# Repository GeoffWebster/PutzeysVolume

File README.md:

Bruno Putzeys Balanced Volume Control / MAS6116 Digital Control
===============================================================

KiCad V8 files for Bruno Putzeys Balanced Pre-amp with integrated MAS6116 Digital Volume Control Chip.

Circuit modifications from original design includes
* Addition of MAS6116 digital Stereo Volume Control in place of dual linear 10Kohm potentiometer
* Addition of inverting unity gain amplifier driver for driven signal for - output pin. Original was balanced output impedance only
* Addition of Unbalanced output (X5) to provide input to headphone amplifier

Original Bruno Putzeys preamplifier used qty 4 of LM4562 + qty 1 of TL072 (as servo)
Alternatives to LM4562 include
* OPA1642AIDR  595-OPA1642AIDR
* OPA1656ID    595-OPA1656ID

Addition of inverting amplifiers within balanced output (Vout-) adds following components into overall circuit:
U7, U8 OPA1656
R38-41 12K 0805 Thin Film
C28, C29 47pF **DNF**

Addition of unbalanced output for use by external headphone amplifier added connector X5 only.

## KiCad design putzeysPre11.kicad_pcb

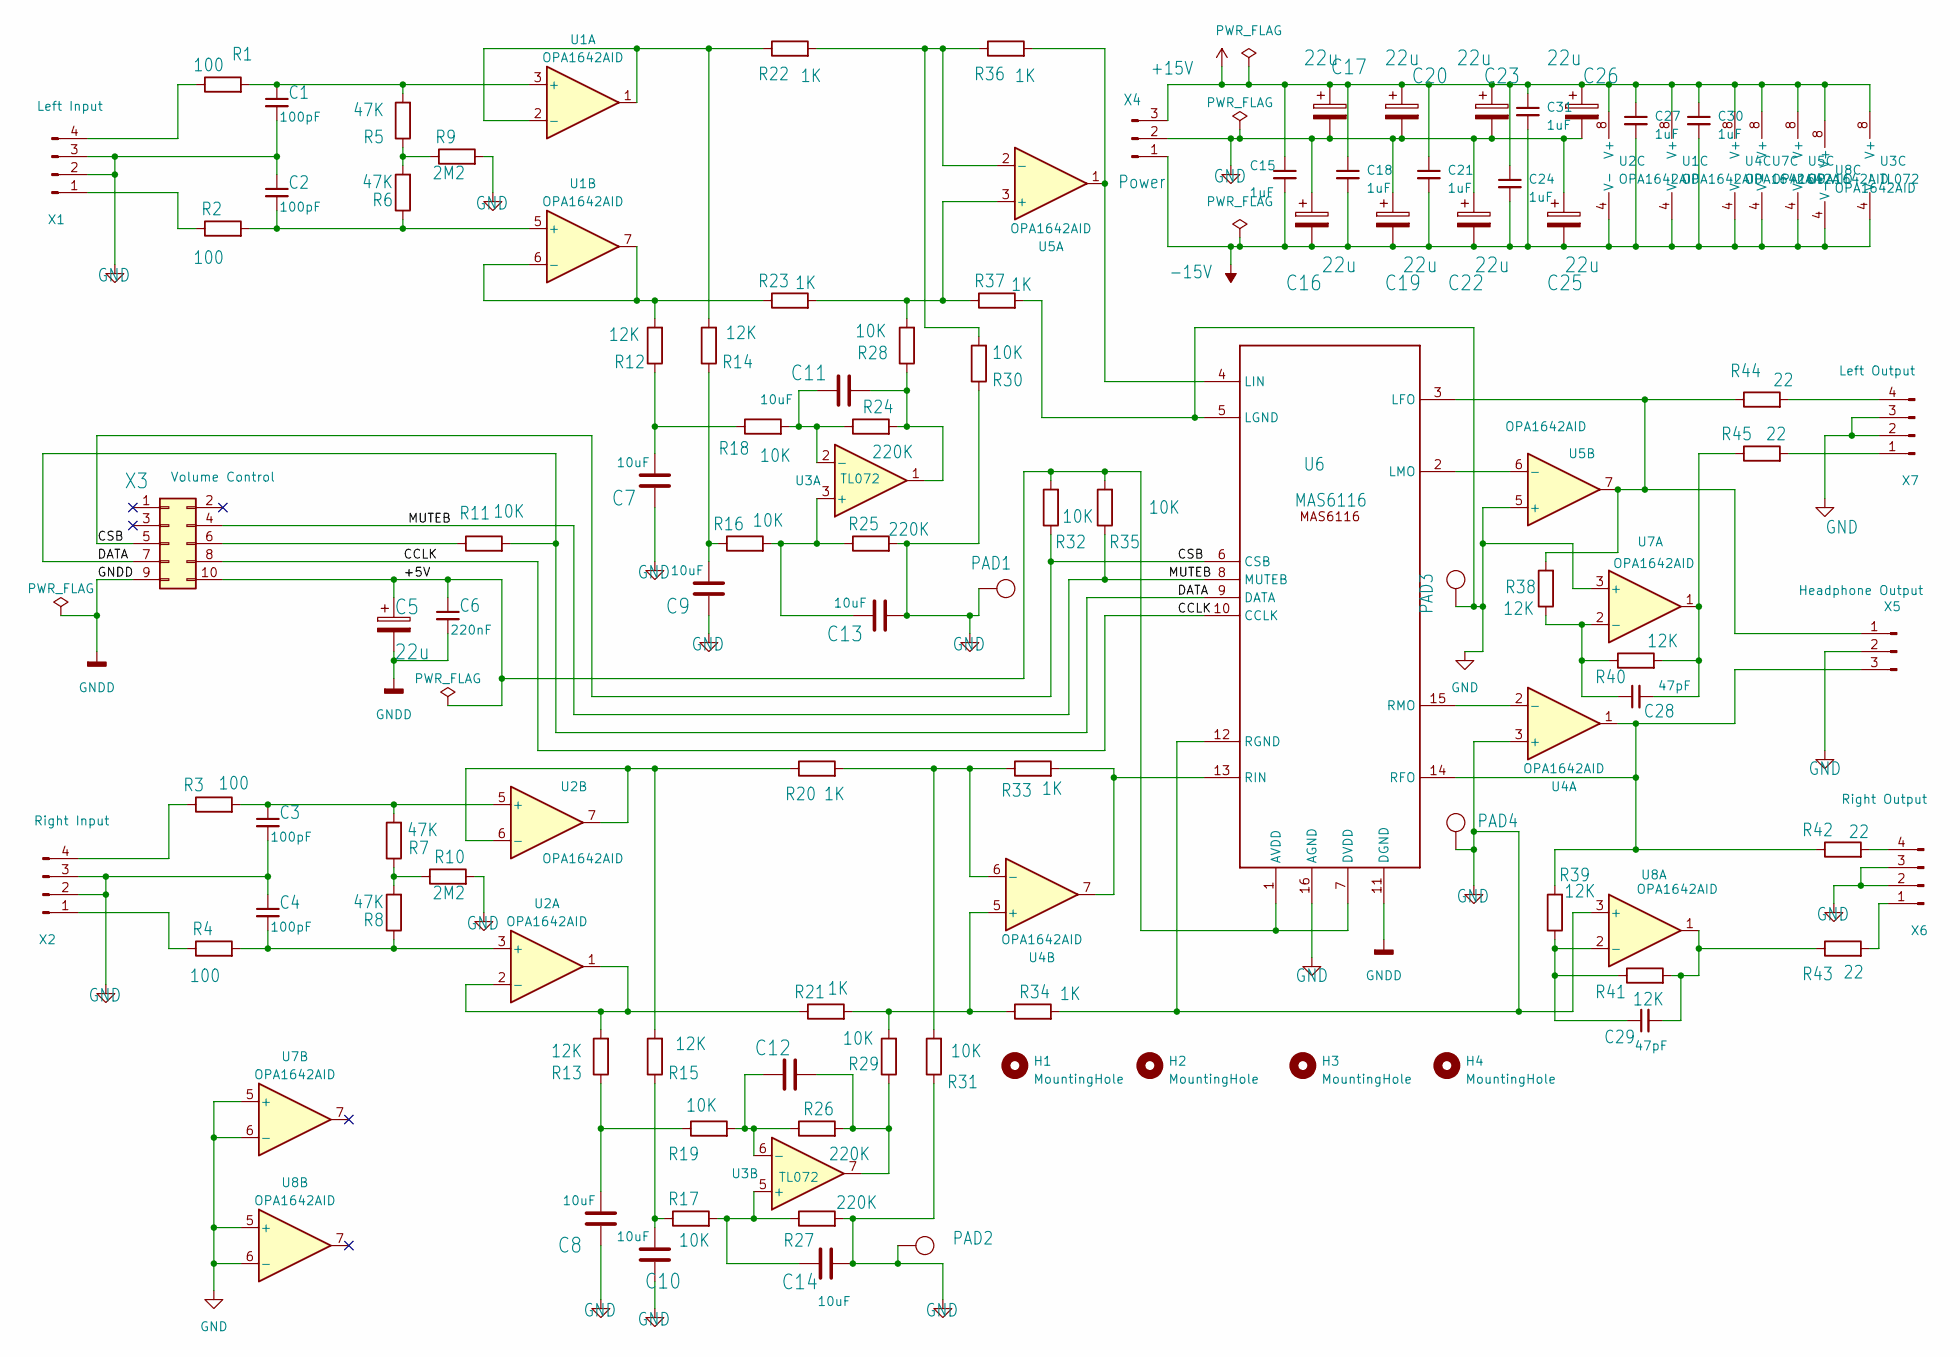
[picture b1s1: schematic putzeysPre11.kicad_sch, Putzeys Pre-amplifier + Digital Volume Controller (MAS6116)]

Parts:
C1, C2, C3, C4: 100pF; C_0805_2012Metric
C5, C16, C17, C19, C20, C22, C23, C25, C26: 22u; CP_Radial_D5.0mm_P2.00mm
C6: 220nF; C_0805_2012Metric
C7, C8, C9, C10, C11, C13, C14: 10uF; C_Radial_D6.3mm_H11.0mm_P2.50mm
C12: C; C_Radial_D6.3mm_H11.0mm_P2.50mm
C15, C18, C21, C24, C27, C30, C31: 1uF; C_1206_3216Metric
C28, C29: 47pF; C_0805_2012Metric
H1, H2, H3, H4: MountingHole; MountingHole_3.2mm_M3
PAD1, PAD2, PAD3, PAD4: 1,6/0,8; TestPoint_THTPad_1.0x1.0mm_Drill0.5mm
R1, R2, R3, R4: 100; R_0805_2012Metric
R5, R6, R7, R8: 47K; R_0805_2012Metric
R9, R10: 2M2; R_0805_2012Metric
R11, R16, R17, R18, R19, R28, R29, R30, R31, R32, R35: 10K; R_0805_2012Metric
R12, R13, R14, R15, R38, R39, R40, R41: 12K; R_0805_2012Metric
R20, R21, R22, R23, R33, R34, R36, R37: 1K; R_0805_2012Metric
R24, R25, R26, R27: 220K; R_0805_2012Metric
R42, R43, R44, R45: 22; R_0805_2012Metric
U1, U2, U4, U5, U8: OPA1642AID; SOIC-8_3.9x4.9mm_P1.27mm
U3: TL072
U6: MAS6116; SOIC-16W_7.5x10.3mm_P1.27mm
U7: OPA1642AID
X1: Left Input; Molex_KK-254_AE-6410-04A_1x04_P2.54mm_Vertical
X2: Right Input; Molex_KK-254_AE-6410-04A_1x04_P2.54mm_Vertical
X3: Volume Control; IDC-Header_2x05_P2.54mm_Vertical
X4: Power; Molex_KK-254_AE-6410-03A_1x03_P2.54mm_Vertical
X5: Headphone Output; Molex_KK-254_AE-6410-03A_1x03_P2.54mm_Vertical
X6: Right Output; Molex_KK-254_AE-6410-04A_1x04_P2.54mm_Vertical
X7: Left Output; Molex_KK-254_AE-6410-04A_1x04_P2.54mm_Vertical

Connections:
+18V: C15.1, C17.1, C18.1, C20.1, C21.1, C23.1, C24.1, C26.1, C27.1, C30.1, C31.1, U1.8 (V+), U2.8 (V+), U3.8 (V+), U4.8 (V+), U5.8 (V+), U7.8 (V+), U8.8 (V+), X4.3
-18V: C15.2, C16.2, C18.2, C19.2, C21.2, C22.2, C24.2, C25.2, C27.2, C30.2, C31.2, U1.4 (V-), U2.4 (V-), U3.4 (V-), U4.4 (V-), U5.4 (V-), U7.4 (V-), U8.4 (V-), X4.1
/+5V: C5.1, C6.1, R32.2, R35.2, U6.1 (AVDD), U6.7 (DVDD), X3.10
/CCLK: U6.10 (CCLK), X3.8
/CSB: R32.1, U6.6 (CSB), X3.5
/DATA: R11.2, U6.9 (DATA), X3.7
/MUTEB: R35.1, U6.8 (MUTEB), X3.4
GND: C1.2, C2.1, C3.2, C4.1, C7.1, C8.1, C9.1, C10.1, C13.1, C14.1, C16.1, C17.2, C19.1, C20.2, C22.1, C23.2, C25.1, C26.2, PAD1., PAD1.1, PAD2., PAD2.1, PAD3., PAD3.1, PAD4., PAD4.1, R9.2, R10.2, R25.2, R27.2, R30.1, R31.1, R34.2, R37.2, U4.3 (+), U5.5 (+), U6.5 (LGND), U6.12 (RGND), U6.16 (AGND), U7.3 (+), U7.5 (+), U7.6 (-), U8.3 (+), U8.5 (+), U8.6 (-), X1.2, X1.3, X2.2, X2.3, X4.2, X5.2, X6.2, X6.3, X7.2, X7.3
GNDD: C5.2, C6.2, U6.11 (DGND), X3.9
unnamed: C7.2, R12.1, R18.1
unnamed: C8.2, R13.1, R19.1
unnamed: C9.2, R14.1, R16.1
unnamed: C10.2, R15.1, R17.1
unnamed: C11.1, R24.2, R28.1, U3.1
unnamed: C12.1, R26.2, R29.1, U3.7
unnamed: C28.2, R40.2, R45.1, U7.1
unnamed: C29.2, R41.2, R43.1, U8.1
unnamed: R5.1, R6.2, R9.1
unnamed: R7.1, R8.2, R10.1
unnamed: C1.1, R1.2, R5.2, U1.3 (+)
unnamed: R14.2, R22.1, U1.1, U1.2 (-)
unnamed: C2.2, R2.2, R6.1, U1.5 (+)
unnamed: R12.2, R23.1, U1.6 (-), U1.7
unnamed: C4.2, R4.2, R8.1, U2.3 (+)
unnamed: R13.2, R21.1, U2.1, U2.2 (-)
unnamed: C3.1, R3.2, R7.2, U2.5 (+)
unnamed: R15.2, R20.1, U2.6 (-), U2.7
unnamed: C13.2, R16.2, R25.1, U3.3 (+)
unnamed: C11.2, R18.2, R24.1, U3.2 (-)
unnamed: C14.2, R17.2, R27.1, U3.5 (+)
unnamed: C12.2, R19.2, R26.1, U3.6 (-)
unnamed: U4.2 (-), U6.15 (RMO)
unnamed: R21.2, R29.2, R34.1, U4.5 (+)
unnamed: R20.2, R31.2, R33.1, U4.6 (-)
unnamed: R23.2, R28.2, R37.1, U5.3 (+)
unnamed: R22.2, R30.2, R36.1, U5.2 (-)
unnamed: U5.6 (-), U6.2 (LMO)
unnamed: R38.2, R44.1, U5.7, U6.3 (LFO), X5.1
unnamed: R36.2, U5.1, U6.4 (LIN)
unnamed: R39.2, R42.1, U4.1, U6.14 (RFO), X5.3
unnamed: R33.2, U4.7, U6.13 (RIN)
unnamed: C28.1, R38.1, R40.1, U7.2 (-)
unnamed: C29.1, R39.1, R41.1, U8.2 (-)
unnamed: R2.1, X1.1
unnamed: R1.1, X1.4
unnamed: R4.1, X2.1
unnamed: R3.1, X2.4
unnamed: R11.1, X3.6
unnamed: R43.2, X6.1
unnamed: R42.2, X6.4
unnamed: R45.2, X7.1
unnamed: R44.2, X7.4
Unconnected-(U7-Pad7): U7.7

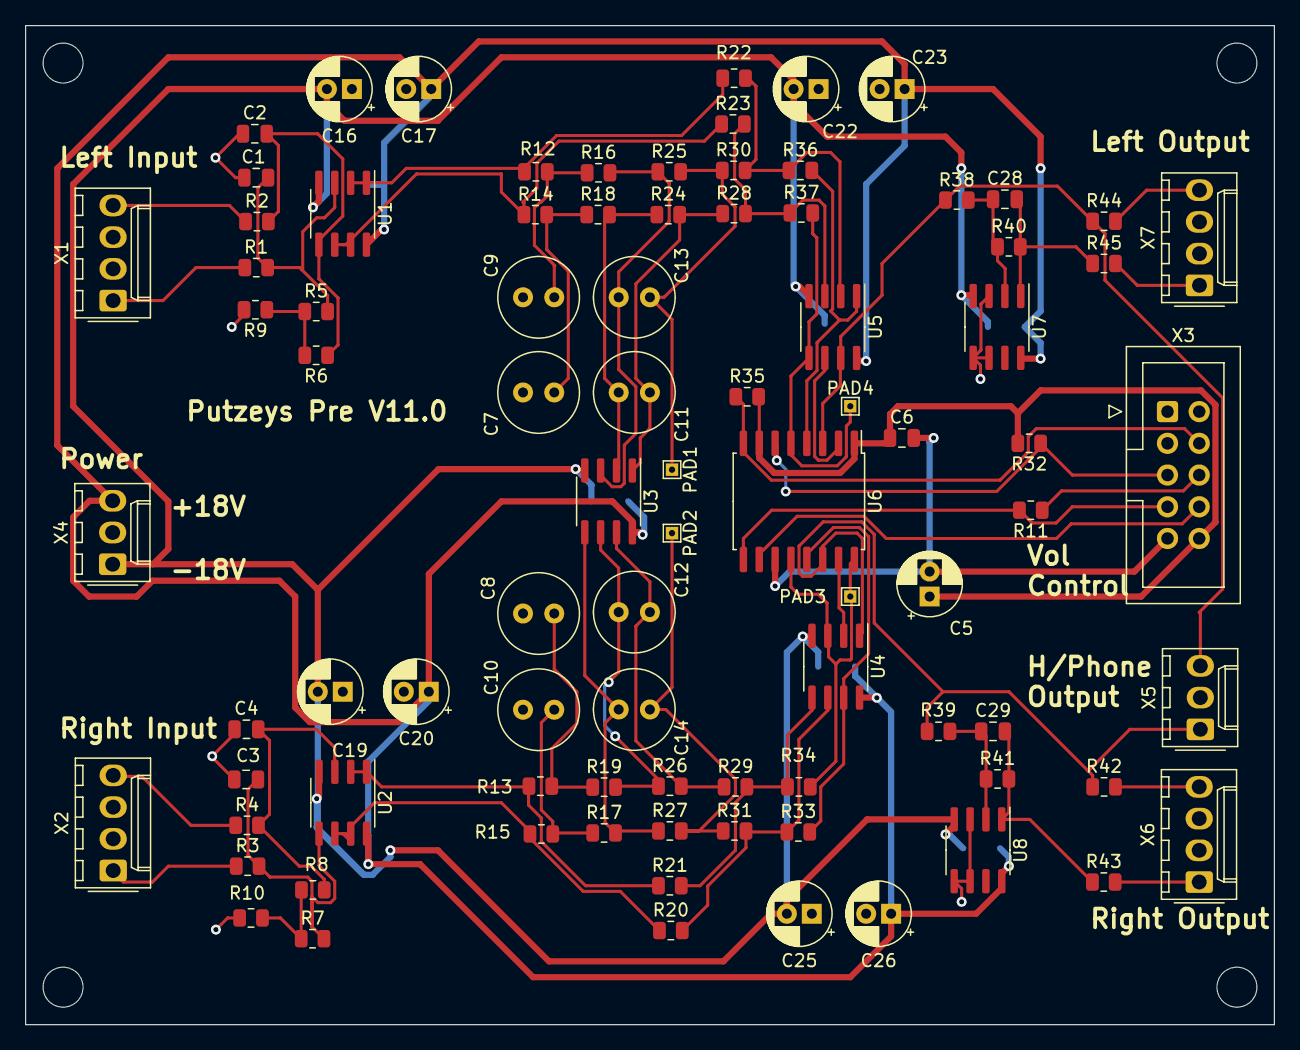
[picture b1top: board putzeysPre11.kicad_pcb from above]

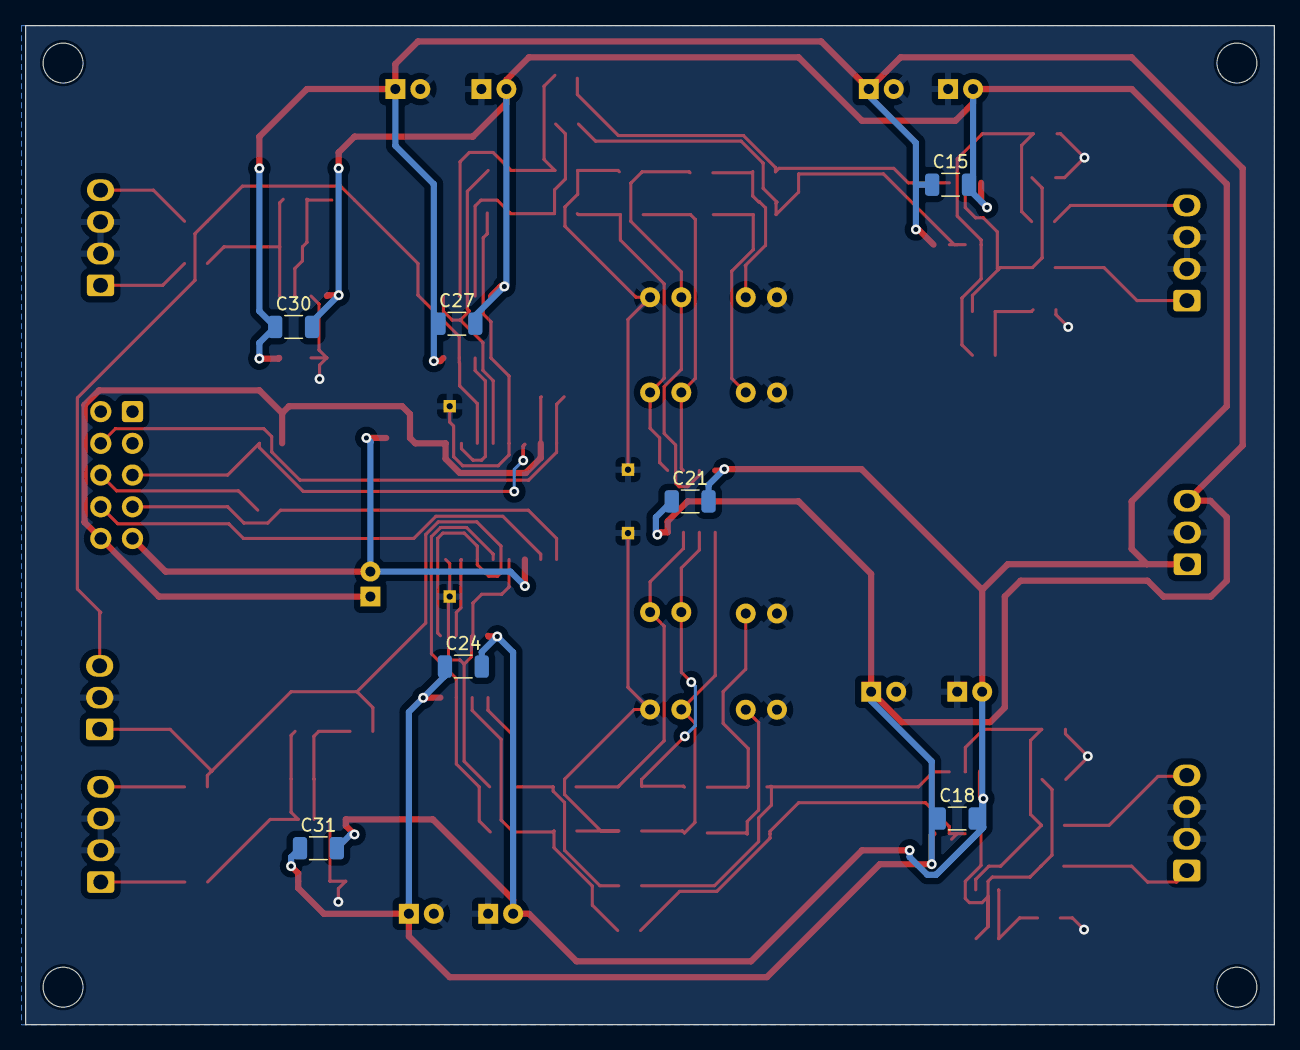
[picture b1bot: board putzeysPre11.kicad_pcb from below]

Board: 2 copper layers, 100.0 x 80.0 mm, 99 parts (7 on the bottom side), 52 nets.

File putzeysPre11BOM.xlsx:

Ref | Qty | Value | Cmp name | Footprint | Description
C1, C2, C3, C4, C28, C29 | 6 | 100pF | C-EUC0805 | Capacitor_SMD:C_0805_2012Metric
C5, C16, C17, C19, C20, C22, C23, C25, C26 | 9 | 22uF 63V | EEU-P2.0 | Capacitor_THT:CP_Radial_D5.0mm_P2.00mm
C6 | 1 | 220nF | C-EUC0805 | Capacitor_SMD:C_0805_2012Metric
C7, C8, C9, C10, C11, C12, C13, C14 | 8 | 10uF 50V | C | Capacitor_THT:C_Radial_D6.3mm_H11.0mm_P2.50mm | Unpolarized capacitor
C15, C18, C21, C24, C27, C30, C31 | 7 | 1uF | C_Small | Capacitor_SMD:C_1206_3216Metric | Unpolarized capacitor, small symbol
R1, R2, R3, R4 | 4 | 100 | R-EU_R0805 | Resistor_SMD:R_0805_2012Metric
R5, R6, R7, R8 | 4 | 47K | R-EU_R0805 | Resistor_SMD:R_0805_2012Metric
R9, R10 | 2 | 2M2 | R-EU_R0805 | Resistor_SMD:R_0805_2012Metric
R11, R16, R17, R18, R19, R28, R29, R30, R31, R32, R35 | 11 | 10K | R-EU_R0805 | Resistor_SMD:R_0805_2012Metric
R12, R13, R14, R15 | 4 | 12K | R-EU_R0805 | Resistor_SMD:R_0805_2012Metric
R20, R21, R22, R23, R33, R34, R36, R37, R38, R39, R40, R41 | 12 | 1K | R-EU_R0805 | Resistor_SMD:R_0805_2012Metric
R24, R25, R26, R27 | 4 | 220K | R-EU_R0805 | Resistor_SMD:R_0805_2012Metric
R42, R43, R44, R45 | 4 | 22 | R-EU_R0805 | Resistor_SMD:R_0805_2012Metric
U1, U2, U4, U5, U7, U8 | 6 | OPA1656AID | OPA2156xD | Package_SO:SOIC-8_3.9x4.9mm_P1.27mm | Dual 36V, Ultra Low Noise, Rail-to-Rail Input/Output, Low Offset Voltage, Opera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
U3 | 1 | TL072 | TL072 |  | Dual Low-Noise JFET-Input Operational Amplifiers, DIP-8/SOIC-8
X1, X2, X6, X7 | 4 | 22-23-2041 | 22-23-2041 | Connector_Molex:Molex_KK-254_AE-6410-04A_1x04_P2.54mm_Vertical
X3 | 1 | 2-1761603-3 | 2-1761603-3 | Connector_IDC:IDC-Header_2x05_P2.54mm_Vertical
X4, X5 | 2 | 22-23-2031 | 22-23-2031 | Connector_Molex:Molex_KK-254_AE-6410-03A_1x03_P2.54mm_Vertical

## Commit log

2024-03-04 Add files via upload
    Added Mouser Part Numbers
2024-03-04 Update README.md
    Added details of amendments to original design
